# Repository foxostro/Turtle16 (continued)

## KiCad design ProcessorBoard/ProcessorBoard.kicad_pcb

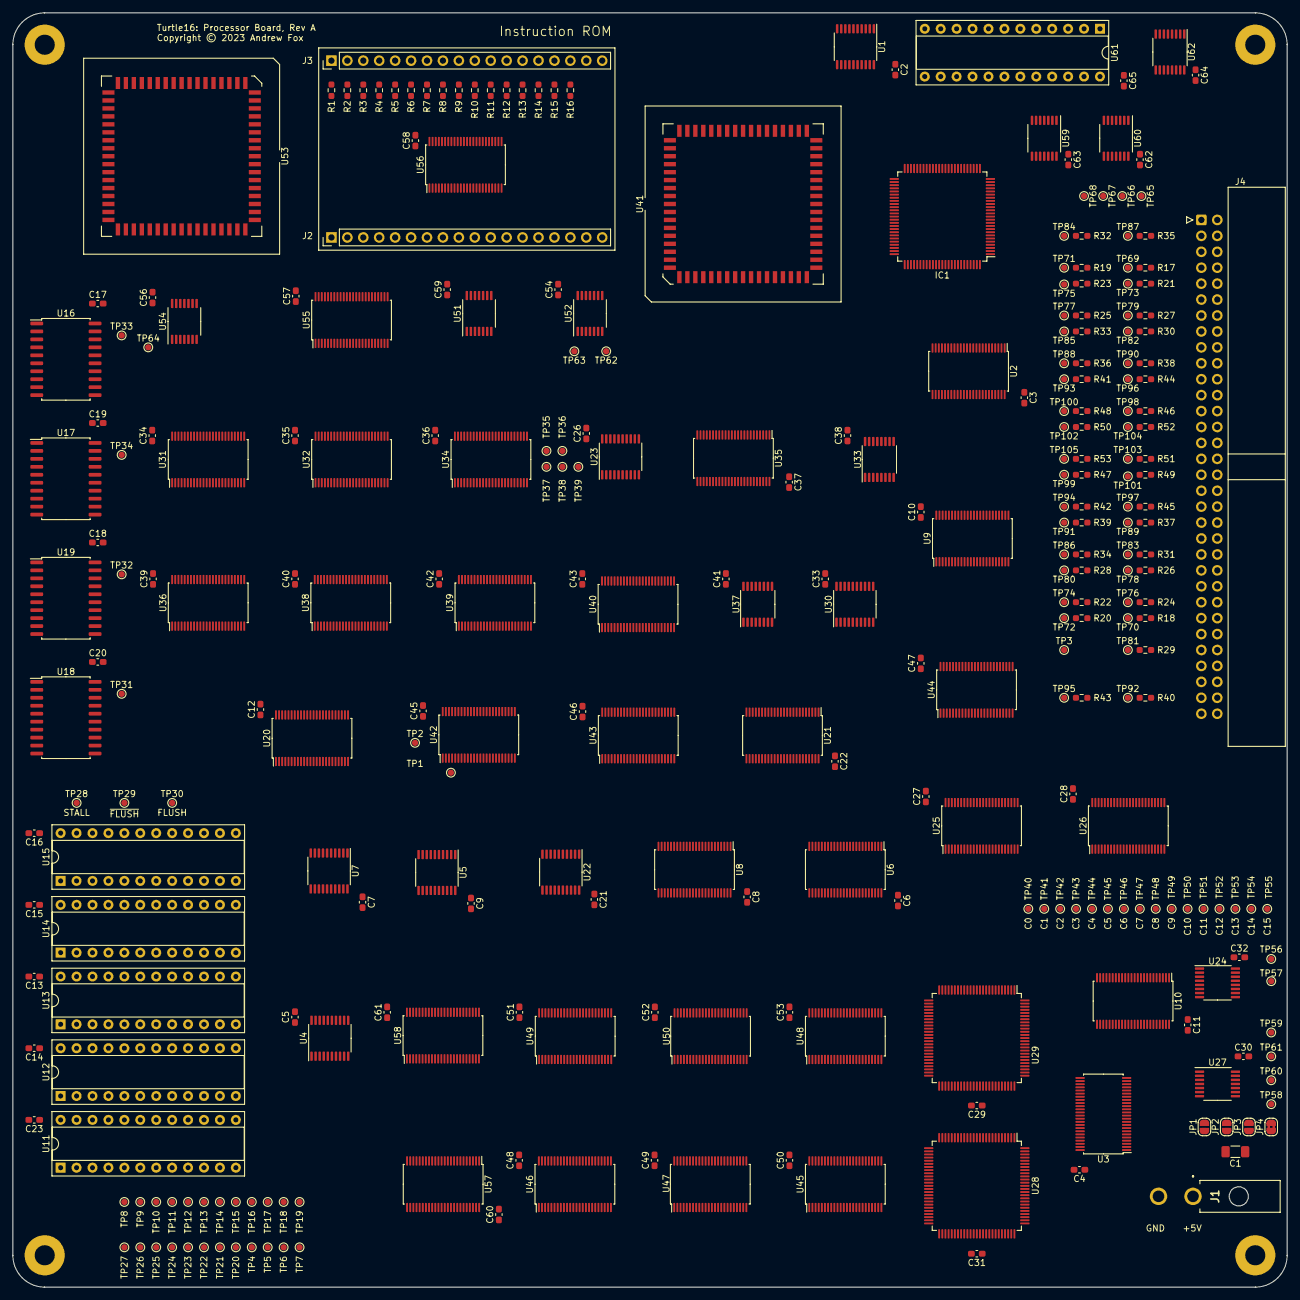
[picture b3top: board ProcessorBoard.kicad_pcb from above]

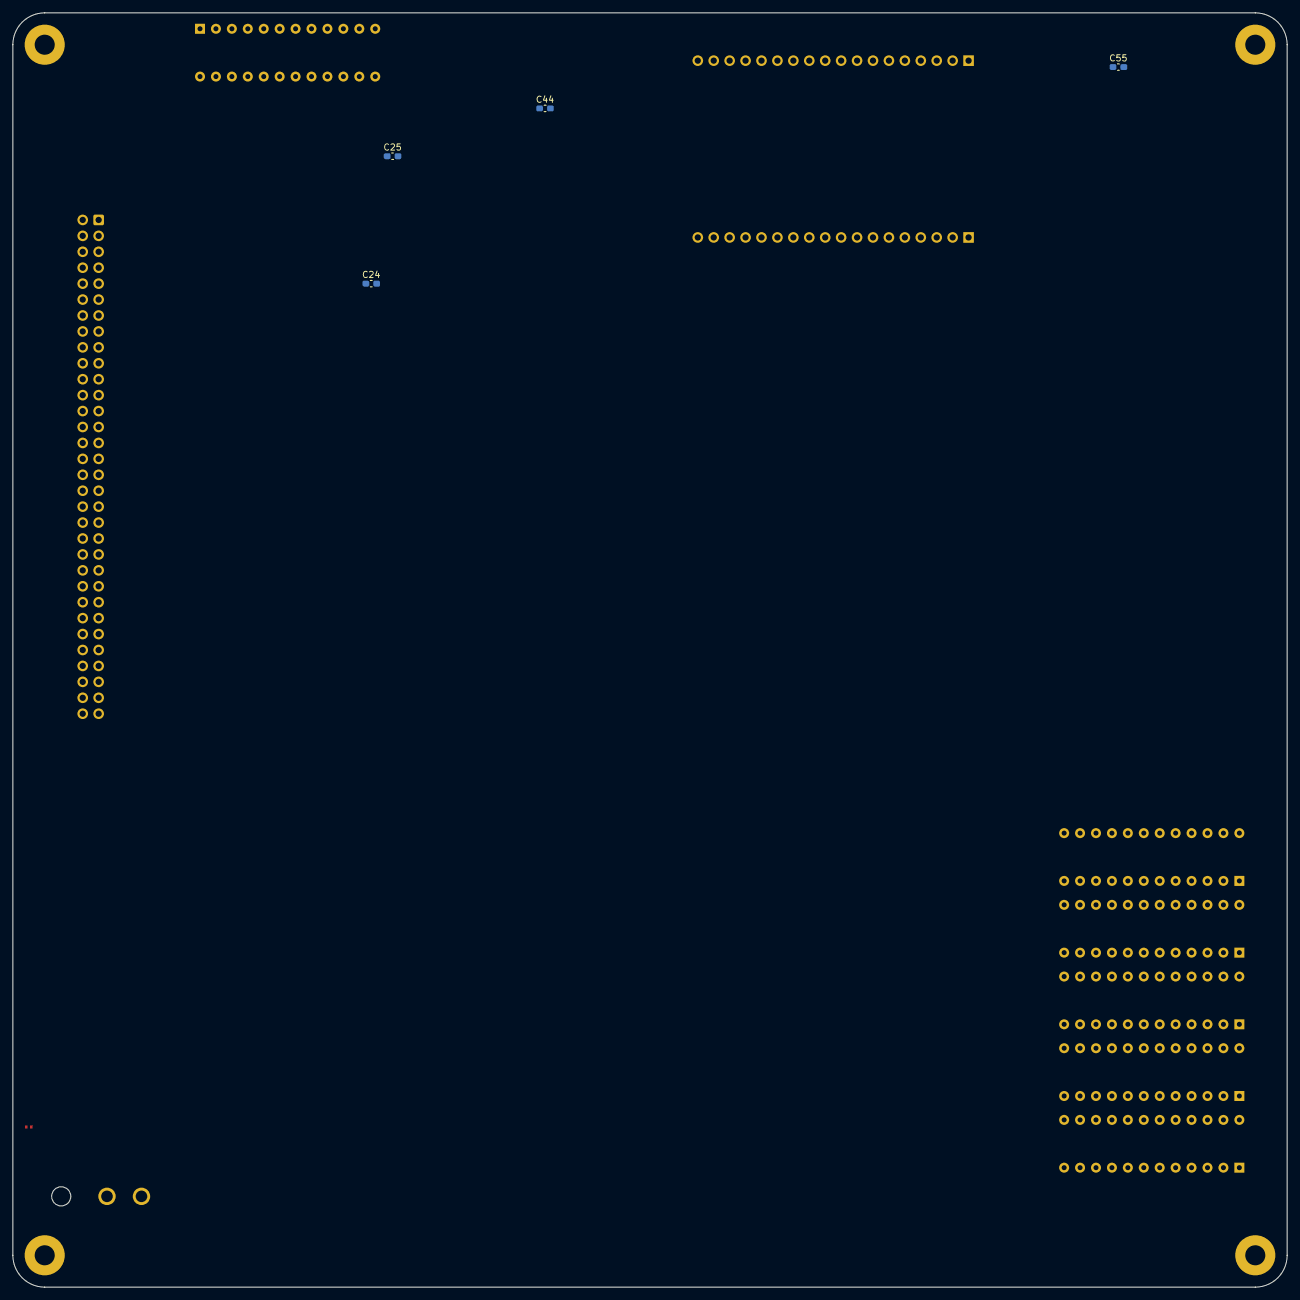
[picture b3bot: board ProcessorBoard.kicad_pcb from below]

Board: 8 copper layers, 203.2 x 203.2 mm, 298 parts (4 on the bottom side), 483 nets, no tracks yet.

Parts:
C1: 100µF; C_1206_3216Metric_Pad1.33x1.80mm_HandSolder
C2, C3, C4, C5, C6, C7, C8, C9, C10, C11, C12, C13, C14, C15, C16, C17, C18, C19, C20, C21, C22, C23, C24, C25, C33, C34, C35, C36, C37, C38, C39, C40, C41, C42, C43, C44, C45, C46, C47, C48, C49, C50, C51, C52, C53, C54, C55, C56, C57, C58, C59, C60, C61, C62, C63, C64, C65: 0.1uF; C_0603_1608Metric_Pad1.08x0.95mm_HandSolder
C26, C27, C28, C29, C30, C31, C32: 0.1µF; C_0603_1608Metric_Pad1.08x0.95mm_HandSolder
H1, H2, H3, H4: MountingHole_Pad; MountingHole_3.2mm_M3_Pad
IC1: 7028L20PFGI; TQFP-100_14x14mm_P0.5mm
J1: Power; 172448-0002
J2: UpperHeader; PinHeader_1x18_P2.54mm_Vertical
J3: LowerHeader; PinHeader_1x18_P2.54mm_Vertical
J4: 71922-164LF; IDC-Header_2x32_P2.54mm_Horizontal
JP1, JP2, JP3: SolderJumper_2_Open; SolderJumper-2_P1.3mm_Open_RoundedPad1.0x1.5mm
JP4: SolderJumper_2_Bridged; SolderJumper-2_P1.3mm_Bridged2Bar_RoundedPad1.0x1.5mm
R1, R2, R3, R4, R5, R6, R7, R8, R9, R10, R11, R12, R13, R14, R15, R16, R17, R18, R19, R20, R21, R22, R23, R24, R25, R26, R27, R28, R29, R30, R31, R32, R33, R34, R35, R36, R37, R38, R39, R41, R42, R44, R45, R46, R47, R48, R49, R50, R51, R52, R53: 10K; R_0603_1608Metric_Pad0.98x0.95mm_HandSolder
R40, R43: 1K; R_0603_1608Metric_Pad0.98x0.95mm_HandSolder
TP1: ~{MemStoreIn}; TestPoint_Pad_D1.0mm
TP2: ~{MemLoadIn}; TestPoint_Pad_D1.0mm
TP3: ~{AssertData}; TestPoint_Pad_D1.0mm
TP4: Ctl_Mid0; TestPoint_Pad_D1.0mm
TP5: Ctl_Mid1; TestPoint_Pad_D1.0mm
TP6: Ctl_Mid2; TestPoint_Pad_D1.0mm
TP7: Ctl_Mid3; TestPoint_Pad_D1.0mm
TP8: Ctl_Mid4; TestPoint_Pad_D1.0mm
TP9: Ctl_Mid5; TestPoint_Pad_D1.0mm
TP10: Ctl_Mid6; TestPoint_Pad_D1.0mm
TP11: Ctl_Mid7; TestPoint_Pad_D1.0mm
TP12: Ctl_Mid8; TestPoint_Pad_D1.0mm
TP13: Ctl_Mid9; TestPoint_Pad_D1.0mm
TP14: Ctl_Mid10; TestPoint_Pad_D1.0mm
TP15: Ctl_Mid11; TestPoint_Pad_D1.0mm
TP16: Ctl_Mid12; TestPoint_Pad_D1.0mm
TP17: Ctl_Mid13; TestPoint_Pad_D1.0mm
TP18: Ctl_Mid14; TestPoint_Pad_D1.0mm
TP19: Ctl_Mid15; TestPoint_Pad_D1.0mm
TP20: Ctl_Mid16; TestPoint_Pad_D1.0mm
TP21: Ctl_Mid17; TestPoint_Pad_D1.0mm
TP22: Ctl_Mid18; TestPoint_Pad_D1.0mm
TP23: Ctl_Mid19; TestPoint_Pad_D1.0mm
TP24: Ctl_Mid20; TestPoint_Pad_D1.0mm
TP25: Ctl_Mid21; TestPoint_Pad_D1.0mm
TP26: Ctl_Mid22; TestPoint_Pad_D1.0mm
TP27: Ctl_Mid23; TestPoint_Pad_D1.0mm
TP28: STALL; TestPoint_Pad_D1.0mm
TP29: ~{FLUSH}; TestPoint_Pad_D1.0mm
TP30: FLUSH; TestPoint_Pad_D1.0mm
TP31: SEL_B_MATCHES_SEL_C_MEM; TestPoint_Pad_D1.0mm
TP32: SEL_A_MATCHES_SEL_C_MEM; TestPoint_Pad_D1.0mm
TP33: SEL_A_MATCHES_SEL_C_EX; TestPoint_Pad_D1.0mm
TP34: SEL_B_MATCHES_SEL_C_EX; TestPoint_Pad_D1.0mm
TP35: Phi2; TestPoint_Pad_D1.0mm
TP36: Phi1a; TestPoint_Pad_D1.0mm
TP37: Phi1b; TestPoint_Pad_D1.0mm
TP38: Phi1c; TestPoint_Pad_D1.0mm
TP39: Phi1d; TestPoint_Pad_D1.0mm
TP40: C0; TestPoint_Pad_D1.0mm
TP41: C1; TestPoint_Pad_D1.0mm
TP42: C2; TestPoint_Pad_D1.0mm
TP43: C3; TestPoint_Pad_D1.0mm
TP44: C4; TestPoint_Pad_D1.0mm
TP45: C5; TestPoint_Pad_D1.0mm
TP46: C6; TestPoint_Pad_D1.0mm
TP47: C7; TestPoint_Pad_D1.0mm
TP48: C8; TestPoint_Pad_D1.0mm
TP49: C9; TestPoint_Pad_D1.0mm
TP50: C10; TestPoint_Pad_D1.0mm
TP51: C11; TestPoint_Pad_D1.0mm
TP52: C12; TestPoint_Pad_D1.0mm
TP53: C13; TestPoint_Pad_D1.0mm
TP54: C14; TestPoint_Pad_D1.0mm
TP55: C15; TestPoint_Pad_D1.0mm
TP56, TP57, TP58, TP59, TP60, TP61, TP62: TP; TestPoint_Pad_D1.0mm
TP63: RS1; TestPoint_Pad_D1.0mm
TP64: CLK; TestPoint_Pad_D1.0mm
TP65, TP66, TP67, TP68: TestPoint; TestPoint_Pad_D1.0mm
TP69: Addr0; TestPoint_Pad_D1.0mm
TP70: IO0; TestPoint_Pad_D1.0mm
TP71: Addr1; TestPoint_Pad_D1.0mm
TP72: IO1; TestPoint_Pad_D1.0mm
TP73: Addr2; TestPoint_Pad_D1.0mm
TP74: IO2; TestPoint_Pad_D1.0mm
TP75: Addr3; TestPoint_Pad_D1.0mm
TP76: IO3; TestPoint_Pad_D1.0mm
TP77: Addr4; TestPoint_Pad_D1.0mm
TP78: IO4; TestPoint_Pad_D1.0mm
TP79: Addr5; TestPoint_Pad_D1.0mm
TP80: IO5; TestPoint_Pad_D1.0mm
TP81: Bank0; TestPoint_Pad_D1.0mm
TP82: Addr6; TestPoint_Pad_D1.0mm
TP83: IO6; TestPoint_Pad_D1.0mm
TP84: Bank1; TestPoint_Pad_D1.0mm
TP85: Addr7; TestPoint_Pad_D1.0mm
TP86: IO7; TestPoint_Pad_D1.0mm
TP87: Bank2; TestPoint_Pad_D1.0mm
TP88: Addr8; TestPoint_Pad_D1.0mm
TP89: IO8; TestPoint_Pad_D1.0mm
TP90: Addr9; TestPoint_Pad_D1.0mm
TP91: IO9; TestPoint_Pad_D1.0mm
TP92: ~{MemStore}; TestPoint_Pad_D1.0mm
TP93: Addr10; TestPoint_Pad_D1.0mm
TP94: IO10; TestPoint_Pad_D1.0mm
TP95: ~{MemLoad}; TestPoint_Pad_D1.0mm
TP96: Addr11; TestPoint_Pad_D1.0mm
TP97: IO11; TestPoint_Pad_D1.0mm
TP98: Addr12; TestPoint_Pad_D1.0mm
TP99: IO12; TestPoint_Pad_D1.0mm
TP100: Addr13; TestPoint_Pad_D1.0mm
TP101: IO13; TestPoint_Pad_D1.0mm
TP102: Addr14; TestPoint_Pad_D1.0mm
TP103: IO14; TestPoint_Pad_D1.0mm
TP104: Addr15; TestPoint_Pad_D1.0mm
TP105: IO15; TestPoint_Pad_D1.0mm
U1, U23: 74AHCT245; TSSOP-20_4.4x6.5mm_P0.65mm
U2, U3, U6, U8, U31, U32, U34, U35, U36, U38, U39, U40, U45, U46, U47, U48, U49, U50: 74AHCT16245; TSSOP-48_6.1x12.5mm_P0.5mm
U4: 74ABT574; TSSOP-20_4.4x6.5mm_P0.65mm
U5, U7: 74HC245; TSSOP-20_4.4x6.5mm_P0.65mm
U9, U10, U20, U21, U42, U43, U44, U55, U56, U57, U58: 74ABT16374; TSSOP-48_6.1x12.5mm_P0.5mm
U11, U12, U13, U14, U15: ATF22V10C-7PX; DIP-24_W7.62mm_Socket
U16, U17, U18, U19: 74F521; SOIC-20W_7.5x12.8mm_P1.27mm
U22: 74AHCT574; TSSOP-20_4.4x6.5mm_P0.65mm
U24, U33, U37: 74AHCT138; TSSOP-16_4.4x5mm_P0.65mm
U25, U26: 74ABT16245; TSSOP-48_6.1x12.5mm_P0.5mm
U27: 74AHCT32; TSSOP-14_4.4x5mm_P0.65mm
U28, U29: IDT7024L15PFG; TQFP-100_14x14mm_P0.5mm
U30: 74ABT377; TSSOP-20_4.4x6.5mm_P0.65mm
U41, U53: IDT7381; PLCC-68_SMD-Socket
U51, U54, U59: 74ABT32; TSSOP-14_4.4x5mm_P0.65mm
U52, U60: 74AHCT04; TSSOP-14_4.4x5mm_P0.65mm
U61: ATF22V10C; DIP-24_W7.62mm_Socket
U62: CD74HC173PWR; TSSOP-16_4.4x5mm_P0.65mm

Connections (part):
/EX/A0: U41.1 (A0), U57.2 (1Q1)
/EX/A1: U41.2 (A1), U57.3 (1Q2)
/EX/A2: U41.3 (A2), U57.5 (1Q3)
/EX/A3: U41.4 (A3), U57.6 (1Q4)
/EX/A4: U41.5 (A4), U57.8 (1Q5)
/EX/A5: U41.6 (A5), U57.9 (1Q6)
/EX/A6: U41.7 (A6), U57.11 (1Q7)
/EX/A7: U41.8 (A7), U57.12 (1Q8)
/EX/A8: U41.9 (A8), U57.13 (2Q1)
/EX/A9: U41.10 (A9), U57.14 (2Q2)
/EX/A10: U41.11 (A10), U57.16 (2Q3)
/EX/A11: U41.12 (A11), U57.17 (2Q4)
/EX/A12: U41.13 (A12), U57.19 (2Q5)
/EX/A13: U41.14 (A13), U57.20 (2Q6)
/EX/A14: U41.15 (A14), U57.22 (2Q7)
/EX/A15: U41.16 (A15), U57.23 (2Q8)
/EX/ALU/C16: U30.3 (D0), U41.20 (C16)
/EX/ALU/OVF: U30.7 (D2), U41.24 (OVF)
/EX/ALU/RightOp0: U31.2 (1B1), U32.2 (1B1), U34.2 (1B1), U35.2 (1B1), U41.53 (B0)
/EX/ALU/RightOp1: U31.3 (1B2), U32.3 (1B2), U34.3 (1B2), U35.3 (1B2), U41.54 (B1)
/EX/ALU/RightOp2: U31.5 (1B3), U32.5 (1B3), U34.5 (1B3), U35.5 (1B3), U41.55 (B2)
/EX/ALU/RightOp3: U31.6 (1B4), U32.6 (1B4), U34.6 (1B4), U35.6 (1B4), U41.56 (B3)
/EX/ALU/RightOp4: U31.8 (1B5), U32.8 (1B5), U34.8 (1B5), U35.8 (1B5), U41.57 (B4)
/EX/ALU/RightOp5: U31.9 (1B6), U32.9 (1B6), U34.9 (1B6), U35.9 (1B6), U41.58 (B5)
/EX/ALU/RightOp6: U31.11 (1B7), U32.11 (1B7), U34.11 (1B7), U35.11 (1B7), U41.59 (B6)
/EX/ALU/RightOp7: U31.12 (1B8), U32.12 (1B8), U34.12 (1B8), U35.12 (1B8), U41.60 (B7)
/EX/ALU/RightOp8: U31.13 (2B1), U32.13 (2B1), U34.13 (2B1), U35.13 (2B1), U41.61 (B8)
/EX/ALU/RightOp9: U31.14 (2B2), U32.14 (2B2), U34.14 (2B2), U35.14 (2B2), U41.62 (B9)
/EX/ALU/RightOp10: U31.16 (2B3), U32.16 (2B3), U34.16 (2B3), U35.16 (2B3), U41.63 (B10)
/EX/ALU/RightOp11: U31.17 (2B4), U32.17 (2B4), U34.17 (2B4), U35.17 (2B4), U41.64 (B11)
/EX/ALU/RightOp12: U31.19 (2B5), U32.19 (2B5), U34.19 (2B5), U35.19 (2B5), U41.65 (B12)
/EX/ALU/RightOp13: U31.20 (2B6), U32.20 (2B6), U34.20 (2B6), U35.20 (2B6), U41.66 (B13)
/EX/ALU/RightOp14: U31.22 (2B7), U32.22 (2B7), U34.22 (2B7), U35.22 (2B7), U41.67 (B14)
/EX/ALU/RightOp15: U31.23 (2B8), U32.23 (2B8), U34.23 (2B8), U35.23 (2B8), U41.68 (B15)
/EX/ALU/Z: U30.4 (D1), U41.23 (Z)
/EX/B0: U31.47 (1A1), U36.47 (1A1), U58.2 (1Q1)
/EX/B1: U31.46 (1A2), U36.46 (1A2), U58.3 (1Q2)
/EX/B2: U31.44 (1A3), U36.44 (1A3), U58.5 (1Q3)
/EX/B3: U31.43 (1A4), U36.43 (1A4), U58.6 (1Q4)
/EX/B4: U31.41 (1A5), U36.41 (1A5), U58.8 (1Q5)
/EX/B5: U31.40 (1A6), U36.40 (1A6), U58.9 (1Q6)
/EX/B6: U31.38 (1A7), U36.38 (1A7), U58.11 (1Q7)
/EX/B7: U31.37 (1A8), U36.37 (1A8), U58.12 (1Q8)
/EX/B8: U31.36 (2A1), U36.36 (2A1), U58.13 (2Q1)
/EX/B9: U31.35 (2A2), U36.35 (2A2), U58.14 (2Q2)
/EX/B10: U31.33 (2A3), U36.33 (2A3), U58.16 (2Q3)
/EX/B11: U31.32 (2A4), U36.32 (2A4), U58.17 (2Q4)
/EX/B12: U31.30 (2A5), U36.30 (2A5), U58.19 (2Q5)
/EX/B13: U31.29 (2A6), U36.29 (2A6), U58.20 (2Q6)
/EX/B14: U31.27 (2A7), U36.27 (2A7), U58.22 (2Q7)
/EX/B15: U31.26 (2A8), U36.26 (2A8), U58.23 (2Q8)
/EX/Carry: U11.4 (IN), U12.4 (IN), U13.4 (IN), U30.2 (Q0)
/EX/Ctl_MEM14: TP2.1, U1.3 (A1), U42.2 (1Q1)
/EX/Ctl_MEM15: TP1.1, U1.2 (A0), U42.3 (1Q2)
/EX/Ctl_MEM16: U42.5 (1Q3), U59.1
/EX/Ctl_MEM17: U4.9 (D7), U14.4 (IN), U42.6 (1Q4)
/EX/Ctl_MEM18: U4.8 (D6), U42.8 (1Q5)
/EX/Ctl_MEM19: U4.7 (D5), U42.9 (1Q6)
/EX/Ctl_MEM20: U4.6 (D4), U14.5 (IN), U42.11 (1Q7)
/EX/N: U11.1 (IN/CLK), U12.1 (IN/CLK), U13.1 (IN/CLK), U30.9 (Q3)
/EX/OVF: U11.2 (IN), U12.2 (IN), U13.2 (IN), U30.6 (Q2)
/EX/PC_EX0: U38.47 (1A1), U55.2 (1Q1)
/EX/PC_EX1: U38.46 (1A2), U55.3 (1Q2)
/EX/PC_EX2: U38.44 (1A3), U55.5 (1Q3)
/EX/PC_EX3: U38.43 (1A4), U55.6 (1Q4)
/EX/PC_EX4: U38.41 (1A5), U55.8 (1Q5)
/EX/PC_EX5: U38.40 (1A6), U55.9 (1Q6)
/EX/PC_EX6: U38.38 (1A7), U55.11 (1Q7)
/EX/PC_EX7: U38.37 (1A8), U55.12 (1Q8)
/EX/PC_EX8: U38.36 (2A1), U55.13 (2Q1)
/EX/PC_EX9: U38.35 (2A2), U55.14 (2Q2)
/EX/PC_EX10: U38.33 (2A3), U55.16 (2Q3)
/EX/PC_EX11: U38.32 (2A4), U55.17 (2Q4)
/EX/PC_EX12: U38.30 (2A5), U55.19 (2Q5)
/EX/PC_EX13: U38.29 (2A6), U55.20 (2Q6)
/EX/PC_EX14: U38.27 (2A7), U55.22 (2Q7)
/EX/PC_EX15: U38.26 (2A8), U55.23 (2Q8)
/EX/SelC_MEM0: U4.5 (D3), U18.3 (Q0), U19.3 (Q0), U42.13 (2Q1)
/EX/SelC_MEM1: U4.4 (D2), U18.5 (Q1), U19.5 (Q1), U42.14 (2Q2)
/EX/SelC_MEM2: U4.3 (D1), U18.7 (Q2), U19.7 (Q2), U42.16 (2Q3)
/EX/StoreOp_MEM0: U2.23 (2B8), U43.2 (1Q1)
/EX/StoreOp_MEM1: U2.22 (2B7), U43.3 (1Q2)
/EX/StoreOp_MEM2: U2.20 (2B6), U43.5 (1Q3)
/EX/StoreOp_MEM3: U2.19 (2B5), U43.6 (1Q4)
/EX/StoreOp_MEM4: U2.17 (2B4), U43.8 (1Q5)
/EX/StoreOp_MEM5: U2.16 (2B3), U43.9 (1Q6)
/EX/StoreOp_MEM6: U2.14 (2B2), U43.11 (1Q7)
/EX/StoreOp_MEM7: U2.13 (2B1), U43.12 (1Q8)
/EX/StoreOp_MEM8: U2.12 (1B8), U43.13 (2Q1)
/EX/StoreOp_MEM9: U2.11 (1B7), U43.14 (2Q2)
/EX/StoreOp_MEM10: U2.9 (1B6), U43.16 (2Q3)
/EX/StoreOp_MEM11: U2.8 (1B5), U43.17 (2Q4)
/EX/StoreOp_MEM12: U2.6 (1B4), U43.19 (2Q5)
/EX/StoreOp_MEM13: U2.5 (1B3), U43.20 (2Q6)
/EX/StoreOp_MEM14: U2.3 (1B2), U43.22 (2Q7)
/EX/StoreOp_MEM15: U2.2 (1B1), U43.23 (2Q8)
/EX/Y_EX0: U41.43 (F0), U44.47 (1D1), U46.47 (1A1), U49.47 (1A1), U53.53 (B0)
/EX/Y_EX1: U41.42 (F1), U44.46 (1D2), U46.46 (1A2), U49.46 (1A2), U53.54 (B1)
/EX/Y_EX2: U41.41 (F2), U44.44 (1D3), U46.44 (1A3), U49.44 (1A3), U53.55 (B2)
/EX/Y_EX3: U41.40 (F3), U44.43 (1D4), U46.43 (1A4), U49.43 (1A4), U53.56 (B3)
/EX/Y_EX4: U41.39 (F4), U44.41 (1D5), U46.41 (1A5), U49.41 (1A5), U53.57 (B4)
/EX/Y_EX5: U41.38 (F5), U44.40 (1D6), U46.40 (1A6), U49.40 (1A6), U53.58 (B5)
/EX/Y_EX6: U41.37 (F6), U44.38 (1D7), U46.38 (1A7), U49.38 (1A7), U53.59 (B6)
/EX/Y_EX7: U41.36 (F7), U44.37 (1D8), U46.37 (1A8), U49.37 (1A8), U53.60 (B7)
/EX/Y_EX8: U41.35 (F8), U44.36 (2D1), U46.36 (2A1), U49.36 (2A1), U53.61 (B8)
/EX/Y_EX9: U41.34 (F9), U44.35 (2D2), U46.35 (2A2), U49.35 (2A2), U53.62 (B9)
/EX/Y_EX10: U41.33 (F10), U44.33 (2D3), U46.33 (2A3), U49.33 (2A3), U53.63 (B10)
/EX/Y_EX11: U41.32 (F11), U44.32 (2D4), U46.32 (2A4), U49.32 (2A4), U53.64 (B11)
/EX/Y_EX12: U41.31 (F12), U44.30 (2D5), U46.30 (2A5), U49.30 (2A5), U53.65 (B12)
/EX/Y_EX13: U41.30 (F13), U44.29 (2D6), U46.29 (2A6), U49.29 (2A6), U53.66 (B13)
/EX/Y_EX14: U41.29 (F14), U44.27 (2D7), U46.27 (2A7), U49.27 (2A7), U53.67 (B14)
/EX/Y_EX15: U30.8 (D3), U41.28 (F15), U44.26 (2D8), U46.26 (2A8), U49.26 (2A8), U53.68 (B15)
/EX/Y_MEM0: U3.2 (1B1), U10.47 (1D1), U44.2 (1Q1), U47.47 (1A1), U50.47 (1A1)
/EX/Y_MEM1: U3.3 (1B2), U10.46 (1D2), U44.3 (1Q2), U47.46 (1A2), U50.46 (1A2)
/EX/Y_MEM2: U3.5 (1B3), U10.44 (1D3), U44.5 (1Q3), U47.44 (1A3), U50.44 (1A3)
/EX/Y_MEM3: U3.6 (1B4), U10.43 (1D4), U44.6 (1Q4), U47.43 (1A4), U50.43 (1A4)
/EX/Y_MEM4: U3.8 (1B5), U10.41 (1D5), U44.8 (1Q5), U47.41 (1A5), U50.41 (1A5)
/EX/Y_MEM5: U3.9 (1B6), U10.40 (1D6), U44.9 (1Q6), U47.40 (1A6), U50.40 (1A6)
/EX/Y_MEM6: U3.11 (1B7), U10.38 (1D7), U44.11 (1Q7), U47.38 (1A7), U50.38 (1A7)
/EX/Y_MEM7: U3.12 (1B8), U10.37 (1D8), U44.12 (1Q8), U47.37 (1A8), U50.37 (1A8)
/EX/Y_MEM8: U3.13 (2B1), U10.36 (2D1), U44.13 (2Q1), U47.36 (2A1), U50.36 (2A1)
/EX/Y_MEM9: U3.14 (2B2), U10.35 (2D2), U44.14 (2Q2), U47.35 (2A2), U50.35 (2A2)
/EX/Y_MEM10: U3.16 (2B3), U10.33 (2D3), U44.16 (2Q3), U47.33 (2A3), U50.33 (2A3)
/EX/Y_MEM11: U3.17 (2B4), U10.32 (2D4), U44.17 (2Q4), U47.32 (2A4), U50.32 (2A4)
/EX/Y_MEM12: U3.19 (2B5), U10.30 (2D5), U44.19 (2Q5), U47.30 (2A5), U50.30 (2A5)
/EX/Y_MEM13: U3.20 (2B6), U10.29 (2D6), U44.20 (2Q6), U47.29 (2A6), U50.29 (2A6)
/EX/Y_MEM14: U3.22 (2B7), U10.27 (2D7), U44.22 (2Q7), U47.27 (2A7), U50.27 (2A7)
/EX/Y_MEM15: U3.23 (2B8), U10.26 (2D8), U44.23 (2Q8), U47.26 (2A8), U50.26 (2A8)
/EX/Z: U11.3 (IN), U12.3 (IN), U13.3 (IN), U30.5 (Q1)
/EX/sheet5FD8D6EA/StoreOp_EX0: U36.2 (1B1), U38.2 (1B1), U39.2 (1B1), U40.2 (1B1), U43.47 (1D1)
/EX/sheet5FD8D6EA/StoreOp_EX1: U36.3 (1B2), U38.3 (1B2), U39.3 (1B2), U40.3 (1B2), U43.46 (1D2)
/EX/sheet5FD8D6EA/StoreOp_EX2: U36.5 (1B3), U38.5 (1B3), U39.5 (1B3), U40.5 (1B3), U43.44 (1D3)
/EX/sheet5FD8D6EA/StoreOp_EX3: U36.6 (1B4), U38.6 (1B4), U39.6 (1B4), U40.6 (1B4), U43.43 (1D4)
/EX/sheet5FD8D6EA/StoreOp_EX4: U36.8 (1B5), U38.8 (1B5), U39.8 (1B5), U40.8 (1B5), U43.41 (1D5)
/EX/sheet5FD8D6EA/StoreOp_EX5: U36.9 (1B6), U38.9 (1B6), U39.9 (1B6), U40.9 (1B6), U43.40 (1D6)
/EX/sheet5FD8D6EA/StoreOp_EX6: U36.11 (1B7), U38.11 (1B7), U39.11 (1B7), U40.11 (1B7), U43.38 (1D7)
/EX/sheet5FD8D6EA/StoreOp_EX7: U36.12 (1B8), U38.12 (1B8), U39.12 (1B8), U40.12 (1B8), U43.37 (1D8)
/EX/sheet5FD8D6EA/StoreOp_EX8: U36.13 (2B1), U38.13 (2B1), U39.13 (2B1), U40.13 (2B1), U43.36 (2D1)
/EX/sheet5FD8D6EA/StoreOp_EX9: U36.14 (2B2), U38.14 (2B2), U39.14 (2B2), U40.14 (2B2), U43.35 (2D2)
/EX/sheet5FD8D6EA/StoreOp_EX10: U36.16 (2B3), U38.16 (2B3), U39.16 (2B3), U40.16 (2B3), U43.33 (2D3)
/EX/sheet5FD8D6EA/StoreOp_EX11: U36.17 (2B4), U38.17 (2B4), U39.17 (2B4), U40.17 (2B4), U43.32 (2D4)
/EX/sheet5FD8D6EA/StoreOp_EX12: U36.19 (2B5), U38.19 (2B5), U39.19 (2B5), U40.19 (2B5), U43.30 (2D5)
/EX/sheet5FD8D6EA/StoreOp_EX13: U36.20 (2B6), U38.20 (2B6), U39.20 (2B6), U40.20 (2B6), U43.29 (2D6)
/EX/sheet5FD8D6EA/StoreOp_EX14: U36.22 (2B7), U38.22 (2B7), U39.22 (2B7), U40.22 (2B7), U43.27 (2D7)
/EX/sheet5FD8D6EA/StoreOp_EX15: U36.23 (2B8), U38.23 (2B8), U39.23 (2B8), U40.23 (2B8), U43.26 (2D8)
/ID/Ctl_EX0: J4.60, U21.2 (1Q1)
/ID/Ctl_EX1: U21.3 (1Q2), U37.1 (A0)
/ID/Ctl_EX2: U21.5 (1Q3), U37.2 (A1)
/ID/Ctl_EX3: U21.6 (1Q4), U33.1 (A0)
/ID/Ctl_EX4: U21.8 (1Q5), U33.2 (A1)
/ID/Ctl_EX5: U15.4 (IN), U21.9 (1Q6), U30.1 (~E)
/ID/Ctl_EX6: U21.11 (1Q7), U41.44 (C0)
/ID/Ctl_EX7: U21.12 (1Q8), U41.45 (I0)
/ID/Ctl_EX8: U21.13 (2Q1), U41.46 (I1)
/ID/Ctl_EX9: U21.14 (2Q2), U41.47 (I2)
/ID/Ctl_EX10: U21.16 (2Q3), U41.48 (RS0)
/ID/Ctl_EX11: U21.17 (2Q4), U41.49 (RS1)
/ID/Ctl_EX12: U15.5 (IN), U21.19 (2Q5), U52.1, U53.44 (C0)
/ID/Ctl_EX13: U21.20 (2Q6), U53.48 (RS0)
/ID/Ctl_EX14: U21.22 (2Q7), U42.47 (1D1)
/ID/Ctl_EX15: U21.23 (2Q8), U42.46 (1D2)
/ID/Ctl_EX16: U22.12 (Q7), U42.44 (1D3)
/ID/Ctl_EX17: U14.2 (IN), U22.13 (Q6), U42.43 (1D4)
/ID/Ctl_EX18: U22.14 (Q5), U42.41 (1D5)
/ID/Ctl_EX19: U22.15 (Q4), U42.40 (1D6)
/ID/Ctl_EX20: U14.3 (IN), U22.16 (Q3), U42.38 (1D7)
/ID/Ctl_Mid0: TP4.1, U6.47 (1A1), U11.23 (I/O)
/ID/Ctl_Mid1: TP5.1, U6.46 (1A2), U11.22 (I/O)
/ID/Ctl_Mid2: TP6.1, U6.44 (1A3), U11.21 (I/O)
/ID/Ctl_Mid3: TP7.1, U6.43 (1A4), U11.20 (I/O)
/ID/Ctl_Mid4: TP8.1, U6.41 (1A5), U11.19 (I/O)
/ID/Ctl_Mid5: TP9.1, U6.40 (1A6), U11.16 (I/O)
/ID/Ctl_Mid6: TP10.1, U6.38 (1A7), U11.17 (I/O)
/ID/Ctl_Mid7: TP11.1, U6.37 (1A8), U11.14 (I/O)
/ID/Ctl_Mid8: TP12.1, U6.36 (2A1), U11.15 (I/O)
/ID/Ctl_Mid9: TP13.1, U6.35 (2A2), U11.18 (I/O)
/ID/Ctl_Mid10: TP14.1, U6.33 (2A3), U12.19 (I/O)
/ID/Ctl_Mid11: TP15.1, U6.32 (2A4), U12.23 (I/O)
/ID/Ctl_Mid12: TP16.1, U6.30 (2A5), U12.21 (I/O)
/ID/Ctl_Mid13: TP17.1, U6.29 (2A6), U12.20 (I/O)
/ID/Ctl_Mid14: TP18.1, U6.27 (2A7), U12.22 (I/O)
/ID/Ctl_Mid15: TP19.1, U6.26 (2A8), U12.18 (I/O)
/ID/Ctl_Mid16: TP20.1, U5.11 (B7), U12.17 (I/O)
/ID/Ctl_Mid17: TP21.1, U5.12 (B6), U12.16 (I/O)
/ID/Ctl_Mid18: TP22.1, U5.13 (B5), U12.15 (I/O)
/ID/Ctl_Mid19: TP23.1, U5.14 (B4), U12.14 (I/O)
/ID/Ctl_Mid20: TP24.1, U5.15 (B3), U13.23 (I/O)
/ID/Ctl_Mid21: TP25.1, U5.16 (B2), U13.22 (I/O), U14.10 (IN)
/ID/Ctl_Mid22: TP26.1, U5.17 (B1), U13.21 (I/O), U14.11 (IN)
/ID/Ctl_Mid23: TP27.1, U5.18 (B0), U13.20 (I/O)
/ID/FWD_A: U14.21 (I/O), U45.25 (2~OE), U45.48 (1~OE)
/ID/FWD_B: U14.20 (I/O), U48.25 (2~OE), U48.48 (1~OE)
/ID/FWD_EX_TO_A: U14.22 (I/O), U46.25 (2~OE), U46.48 (1~OE)
/ID/FWD_EX_TO_B: U14.19 (I/O), U49.25 (2~OE), U49.48 (1~OE)
/ID/FWD_MEM_TO_A: U14.23 (I/O), U47.25 (2~OE), U47.48 (1~OE)
/ID/FWD_MEM_TO_B: U14.18 (I/O), U50.25 (2~OE), U50.48 (1~OE)
/ID/Hazard Control/FLUSH: TP30.1, U5.19 (CE), U6.25 (2~OE), U6.48 (1~OE), U15.21 (I/O)
/ID/Hazard Control/Hazard Control Comparators/SEL_A_MATCHES_SEL_C_EX: TP33.1, U14.6 (IN), U16.19 (~P=Q)
/ID/Hazard Control/Hazard Control Comparators/SEL_A_MATCHES_SEL_C_MEM: TP32.1, U14.8 (IN), U19.19 (~P=Q)
/ID/Hazard Control/Hazard Control Comparators/SEL_B_MATCHES_SEL_C_EX: TP34.1, U14.7 (IN), U17.19 (~P=Q)
/ID/Hazard Control/Hazard Control Comparators/SEL_B_MATCHES_SEL_C_MEM: TP31.1, U14.9 (IN), U18.19 (~P=Q)
/ID/Hazard Control/STALL: TP28.1, U15.23 (I/O), U53.25 (~ENF), U54.2
/ID/Hazard Control/~FLUSH: TP29.1, U7.19 (CE), U8.25 (2~OE), U8.48 (1~OE), U15.22 (I/O)
/ID/ID Flush/Ctl_ID0: U6.2 (1B1), U8.47 (1A1), U21.47 (1D1)
/ID/ID Flush/Ctl_ID1: U6.3 (1B2), U8.46 (1A2), U21.46 (1D2)
/ID/ID Flush/Ctl_ID2: U6.5 (1B3), U8.44 (1A3), U21.44 (1D3)
/ID/ID Flush/Ctl_ID3: U6.6 (1B4), U8.43 (1A4), U21.43 (1D4)
/ID/ID Flush/Ctl_ID4: U6.8 (1B5), U8.41 (1A5), U21.41 (1D5)
/ID/ID Flush/Ctl_ID5: U6.9 (1B6), U8.40 (1A6), U21.40 (1D6)
/ID/ID Flush/Ctl_ID6: U6.11 (1B7), U8.38 (1A7), U21.38 (1D7)
/ID/ID Flush/Ctl_ID7: U6.12 (1B8), U8.37 (1A8), U21.37 (1D8)
/ID/ID Flush/Ctl_ID8: U6.13 (2B1), U8.36 (2A1), U21.36 (2D1)
/ID/ID Flush/Ctl_ID9: U6.14 (2B2), U8.35 (2A2), U21.35 (2D2)
/ID/ID Flush/Ctl_ID10: U6.16 (2B3), U8.33 (2A3), U21.33 (2D3)
/ID/ID Flush/Ctl_ID11: U6.17 (2B4), U8.32 (2A4), U21.32 (2D4)
/ID/ID Flush/Ctl_ID12: U6.19 (2B5), U8.30 (2A5), U21.30 (2D5)
/ID/ID Flush/Ctl_ID13: U6.20 (2B6), U8.29 (2A6), U21.29 (2D6)
/ID/ID Flush/Ctl_ID14: U6.22 (2B7), U8.27 (2A7), U21.27 (2D7)
/ID/ID Flush/Ctl_ID15: U6.23 (2B8), U8.26 (2A8), U21.26 (2D8)
/ID/ID Flush/Ctl_ID16: U5.9 (A7), U7.11 (B7), U22.9 (D7)
/ID/ID Flush/Ctl_ID17: U5.8 (A6), U7.12 (B6), U22.8 (D6)
/ID/ID Flush/Ctl_ID18: U5.7 (A5), U7.13 (B5), U22.7 (D5)
/ID/ID Flush/Ctl_ID19: U5.6 (A4), U7.14 (B4), U22.6 (D4)
/ID/ID Flush/Ctl_ID20: U5.5 (A3), U7.15 (B3), U22.5 (D3)
/ID/ID Flush/Ctl_ID21: U5.4 (A2), U7.16 (B2), U22.4 (D2)
/ID/ID Flush/Ctl_ID22: U5.3 (A1), U7.17 (B1), U22.3 (D1)
/ID/ID Flush/Ctl_ID23: U5.2 (A0), U7.18 (B0), U22.2 (D0)
/ID/Ins_EX0: U20.2 (1Q1), U32.47 (1A1), U34.47 (1A1), U35.47 (1A1), U39.47 (1A1), U40.36 (2A1)
/ID/Ins_EX1: U20.3 (1Q2), U32.46 (1A2), U34.46 (1A2), U35.46 (1A2), U39.46 (1A2), U40.35 (2A2)
/ID/Ins_EX2: U20.5 (1Q3), U32.44 (1A3), U35.44 (1A3), U39.44 (1A3), U40.33 (2A3)
/ID/Ins_EX3: U20.6 (1Q4), U32.43 (1A4), U35.43 (1A4), U39.43 (1A4), U40.32 (2A4)
/ID/Ins_EX4: U20.8 (1Q5), U32.26 (2A8), U32.27 (2A7), U32.29 (2A6), U32.30 (2A5), U32.32 (2A4), U32.33 (2A3), U32.35 (2A2), U32.36 (2A1), U32.37 (1A8), U32.38 (1A7), U32.40 (1A6), U32.41 (1A5), U35.41 (1A5), U39.41 (1A5), U40.30 (2A5)
/ID/Ins_EX5: U20.9 (1Q6), U35.40 (1A6), U39.40 (1A6), U40.29 (2A6)
/ID/Ins_EX6: U20.11 (1Q7), U35.38 (1A7), U39.38 (1A7), U40.27 (2A7)
/ID/Ins_EX7: U20.12 (1Q8), U35.37 (1A8), U39.26 (2A8), U39.27 (2A7), U39.29 (2A6), U39.30 (2A5), U39.32 (2A4), U39.33 (2A3), U39.35 (2A2), U39.36 (2A1), U39.37 (1A8), U40.26 (2A8)
/ID/Ins_EX8: U16.3 (Q0), U17.3 (Q0), U20.13 (2Q1), U34.44 (1A3), U35.36 (2A1), U42.36 (2D1)
/ID/Ins_EX9: U16.5 (Q1), U17.5 (Q1), U20.14 (2Q2), U34.43 (1A4), U35.35 (2A2), U42.35 (2D2)
/ID/Ins_EX10: U16.7 (Q2), U17.7 (Q2), U20.16 (2Q3), U34.26 (2A8), U34.27 (2A7), U34.29 (2A6), U34.30 (2A5), U34.32 (2A4), U34.33 (2A3), U34.35 (2A2), U34.36 (2A1), U34.37 (1A8), U34.38 (1A7), U34.40 (1A6), U34.41 (1A5), U35.26 (2A8), U35.27 (2A7), U35.29 (2A6), U35.30 (2A5), U35.32 (2A4), U35.33 (2A3), U42.33 (2D3)
/ID/Ins_ID0: U20.47 (1D1), U56.2 (1Q1)
/ID/Ins_ID1: U20.46 (1D2), U56.3 (1Q2)
/ID/Ins_ID2: U17.2 (P0), U18.2 (P0), U20.44 (1D3), U29.59 (A0R), U56.5 (1Q3)
/ID/Ins_ID3: U17.4 (P1), U18.4 (P1), U20.43 (1D4), U29.58 (A1R), U56.6 (1Q4)
/ID/Ins_ID4: U17.6 (P2), U18.6 (P2), U20.41 (1D5), U29.57 (A2R), U56.8 (1Q5)
/ID/Ins_ID5: U16.2 (P0), U19.2 (P0), U20.40 (1D6), U28.59 (A0R), U56.9 (1Q6)
/ID/Ins_ID6: U16.4 (P1), U19.4 (P1), U20.38 (1D7), U28.58 (A1R), U56.11 (1Q7)
/ID/Ins_ID7: U16.6 (P2), U19.6 (P2), U20.37 (1D8), U28.57 (A2R), U56.12 (1Q8)
/ID/Ins_ID8: U20.36 (2D1), U56.13 (2Q1)
/ID/Ins_ID9: U20.35 (2D2), U56.14 (2Q2)
/ID/Ins_ID10: U20.33 (2D3), U56.16 (2Q3)
/ID/Ins_ID11: U11.9 (IN), U12.9 (IN), U13.9 (IN), U56.17 (2Q4)
/ID/Ins_ID12: U11.8 (IN), U12.8 (IN), U13.8 (IN), U56.19 (2Q5)
/ID/Ins_ID13: U11.7 (IN), U12.7 (IN), U13.7 (IN), U56.20 (2Q6)
/ID/Ins_ID14: U11.6 (IN), U12.6 (IN), U13.6 (IN), U15.2 (IN), U56.22 (2Q7)
/ID/Ins_ID15: U11.5 (IN), U12.5 (IN), U13.5 (IN), U15.3 (IN), U56.23 (2Q8)
/MEM/Buffer StoreOp As Bus I/O/~AssertData: TP3.1, U2.25 (2~OE), U2.48 (1~OE), U59.3
/MEM/Ctl_WB17: U4.12 (Q7), U24.1 (A0)
/MEM/Ctl_WB18: U4.13 (Q6), U28.83 (~LBL), U29.83 (~LBL)
/MEM/Ctl_WB19: U4.14 (Q5), U28.84 (~UBL), U29.84 (~UBL)
/MEM/Ctl_WB20: U4.15 (Q4), U27.1
/MEM/SelC_WB0: U4.16 (Q3), U28.66 (A0L), U29.66 (A0L)
/MEM/SelC_WB1: U4.17 (Q2), U28.67 (A1L), U29.67 (A1L)
/MEM/SelC_WB2: U4.18 (Q1), U28.68 (A2L), U29.68 (A2L)
/MEM/StoreOp_WB0: U9.2 (1Q1), U26.47 (1A1)
/MEM/StoreOp_WB1: U9.3 (1Q2), U26.46 (1A2)
/MEM/StoreOp_WB2: U9.5 (1Q3), U26.44 (1A3)
/MEM/StoreOp_WB3: U9.6 (1Q4), U26.43 (1A4)
/MEM/StoreOp_WB4: U9.8 (1Q5), U26.41 (1A5)
/MEM/StoreOp_WB5: U9.9 (1Q6), U26.40 (1A6)
/MEM/StoreOp_WB6: U9.11 (1Q7), U26.38 (1A7)
/MEM/StoreOp_WB7: U9.12 (1Q8), U26.37 (1A8)
/MEM/StoreOp_WB8: U9.13 (2Q1), U26.36 (2A1)
/MEM/StoreOp_WB9: U9.14 (2Q2), U26.35 (2A2)
/MEM/StoreOp_WB10: U9.16 (2Q3), U26.33 (2A3)
/MEM/StoreOp_WB11: U9.17 (2Q4), U26.32 (2A4)
/MEM/StoreOp_WB12: U9.19 (2Q5), U26.30 (2A5)
/MEM/StoreOp_WB13: U9.20 (2Q6), U26.29 (2A6)
/MEM/StoreOp_WB14: U9.22 (2Q7), U26.27 (2A7)
/MEM/StoreOp_WB15: U9.23 (2Q8), U26.26 (2A8)
/MEM/Y_WB0: U10.2 (1Q1), U25.47 (1A1)
/MEM/Y_WB1: U10.3 (1Q2), U25.46 (1A2)
/MEM/Y_WB2: U10.5 (1Q3), U25.44 (1A3)
/MEM/Y_WB3: U10.6 (1Q4), U25.43 (1A4)
/MEM/Y_WB4: U10.8 (1Q5), U25.41 (1A5)
/MEM/Y_WB5: U10.9 (1Q6), U25.40 (1A6)
/MEM/Y_WB6: U10.11 (1Q7), U25.38 (1A7)
/MEM/Y_WB7: U10.12 (1Q8), U25.37 (1A8)
/MEM/Y_WB8: U10.13 (2Q1), U25.36 (2A1)
/MEM/Y_WB9: U10.14 (2Q2), U25.35 (2A2)
/MEM/Y_WB10: U10.16 (2Q3), U25.33 (2A3)
/MEM/Y_WB11: U10.17 (2Q4), U25.32 (2A4)
/MEM/Y_WB12: U10.19 (2Q5), U25.30 (2A5)
/MEM/Y_WB13: U10.20 (2Q6), U25.29 (2A6)
/MEM/Y_WB14: U10.22 (2Q7), U25.27 (2A7)
/MEM/Y_WB15: U10.23 (2Q8), U25.26 (2A8)
/MEM/~AssertCtl: U1.19 (CE), U59.2, U60.4
/Memory/Addr0: IC1.92 (A0L), J4.7, R17.1, TP69.1, U3.47 (1A1), U61.1 (IN/CLK)
/Memory/Addr1: IC1.93 (A1L), J4.8, R19.1, TP71.1, U3.46 (1A2), U61.2 (IN)
/Memory/Addr2: IC1.94 (A2L), J4.9, R21.1, TP73.1, U3.44 (1A3), U61.3 (IN)
/Memory/Addr3: IC1.95 (A3L), J4.10, R23.1, TP75.1, U3.43 (1A4), U61.4 (IN)
/Memory/Addr4: IC1.96 (A4L), J4.13, R25.1, TP77.1, U3.41 (1A5), U61.5 (IN)
/Memory/Addr5: IC1.97 (A5L), J4.14, R27.1, TP79.1, U3.40 (1A6), U61.6 (IN)
/Memory/Addr6: IC1.98 (A6L), J4.15, R30.1, TP82.1, U3.38 (1A7), U61.7 (IN)
/Memory/Addr7: IC1.99 (A7L), J4.16, R33.1, TP85.1, U3.37 (1A8), U61.8 (IN)
/Memory/Addr8: IC1.100 (A8L), J4.19, R36.1, TP88.1, U3.36 (2A1), U61.9 (IN)
/Memory/Addr9: IC1.1 (A9L), J4.20, R38.1, TP90.1, U3.35 (2A2), U61.10 (IN)
/Memory/Addr10: IC1.2 (A10L), J4.21, R41.1, TP93.1, U3.33 (2A3), U61.11 (IN)
/Memory/Addr11: IC1.3 (A11L), J4.22, R44.1, TP96.1, U3.32 (2A4), U61.13 (IN/~OE)
/Memory/Addr12: IC1.4 (A12L), J4.25, R46.1, TP98.1, U3.30 (2A5), U61.14 (I/O)
/Memory/Addr13: IC1.5 (A13L), J4.26, R48.1, TP100.1, U3.29 (2A6), U61.15 (I/O)
/Memory/Addr14: IC1.6 (A14L), J4.27, R50.1, TP102.1, U3.27 (2A7), U61.16 (I/O)
/Memory/Addr15: IC1.7 (A15L), J4.28, R52.1, TP104.1, U3.26 (2A8), U61.17 (I/O)
/Memory/Bank0: J4.1, R29.1, TP81.1, U61.18 (I/O), U62.3 (Q0)
/Memory/Bank1: J4.2, R32.1, TP84.1, U61.19 (I/O), U62.4 (Q1)
/Memory/Bank2: J4.3, R35.1, TP87.1, U61.20 (I/O), U62.5 (Q2)
/Memory/IO0: IC1.37 (I/O0L), J4.51, R18.1, TP70.1, U2.26 (2A8), U9.47 (1D1), U62.14 (D0)
/Memory/IO1: IC1.36 (I/O1L), J4.52, R20.1, TP72.1, U2.27 (2A7), U9.46 (1D2), U62.13 (D1)
/Memory/IO2: IC1.34 (I/O2L), J4.49, R22.1, TP74.1, U2.29 (2A6), U9.44 (1D3), U62.12 (D2)
/Memory/IO3: IC1.33 (I/O3L), J4.50, R24.1, TP76.1, U2.30 (2A5), U9.43 (1D4), U62.11 (D3)
/Memory/IO4: IC1.32 (I/O4L), J4.45, R26.1, TP78.1, U2.32 (2A4), U9.41 (1D5)
/Memory/IO5: IC1.31 (I/O5L), J4.46, R28.1, TP80.1, U2.33 (2A3), U9.40 (1D6)
/Memory/IO6: IC1.30 (I/O6L), J4.43, R31.1, TP83.1, U2.35 (2A2), U9.38 (1D7)
/Memory/IO7: IC1.29 (I/O7L), J4.44, R34.1, TP86.1, U2.36 (2A1), U9.37 (1D8)
/Memory/IO8: IC1.27 (I/O8L), J4.39, R37.1, TP89.1, U2.37 (1A8), U9.36 (2D1)
/Memory/IO9: IC1.26 (I/O9L), J4.40, R39.1, TP91.1, U2.38 (1A7), U9.35 (2D2)
/Memory/IO10: IC1.25 (I/O10L), J4.37, R42.1, TP94.1, U2.40 (1A6), U9.33 (2D3)
/Memory/IO11: IC1.24 (I/O11L), J4.38, R45.1, TP97.1, U2.41 (1A5), U9.32 (2D4)
/Memory/IO12: IC1.23 (I/O12L), J4.33, R47.1, TP99.1, U2.43 (1A4), U9.30 (2D5)
/Memory/IO13: IC1.22 (I/O13L), J4.34, R49.1, TP101.1, U2.44 (1A3), U9.29 (2D6)
/Memory/IO14: IC1.21 (I/O14L), J4.31, R51.1, TP103.1, U2.46 (1A2), U9.27 (2D7)
/Memory/IO15: IC1.20 (I/O15L), J4.32, R53.1, TP105.1, U2.47 (1A1), U9.26 (2D8)
/Memory/Ins_IF0: IC1.39 (I/O0R), J3.1, R1.1, U56.47 (1D1)
/Memory/Ins_IF1: IC1.40 (I/O1R), J3.2, R2.1, U56.46 (1D2)
/Memory/Ins_IF2: IC1.41 (I/O2R), J3.3, R3.1, U56.44 (1D3)
/Memory/Ins_IF3: IC1.42 (I/O3R), J3.4, R4.1, U56.43 (1D4)
/Memory/Ins_IF4: IC1.43 (I/O4R), J3.5, R5.1, U56.41 (1D5)
/Memory/Ins_IF5: IC1.44 (I/O5R), J3.6, R6.1, U56.40 (1D6)
/Memory/Ins_IF6: IC1.45 (I/O6R), J3.7, R7.1, U56.38 (1D7)
/Memory/Ins_IF7: IC1.47 (I/O7R), J3.8, R8.1, U56.37 (1D8)
/Memory/Ins_IF8: IC1.48 (I/O8R), J3.9, R9.1, U56.36 (2D1)
/Memory/Ins_IF9: IC1.49 (I/O9R), J3.10, R10.1, U56.35 (2D2)
/Memory/Ins_IF10: IC1.51 (I/O10R), J3.11, R11.1, U56.33 (2D3)
/Memory/Ins_IF11: IC1.52 (I/O11R), J3.12, R12.1, U56.32 (2D4)
/Memory/Ins_IF12: IC1.53 (I/O12R), J3.13, R13.1, U56.30 (2D5)
/Memory/Ins_IF13: IC1.54 (I/O13R), J3.14, R14.1, U56.29 (2D6)
/Memory/Ins_IF14: IC1.55 (I/O14R), J3.15, R15.1, U56.27 (2D7)
/Memory/Ins_IF15: IC1.56 (I/O15R), J3.16, R16.1, U56.26 (2D8)
/Memory/PC0: IC1.84 (A0R), J2.1, U53.1 (A0), U53.43 (F0), U55.47 (1D1)
/Memory/PC1: IC1.83 (A1R), J2.2, U53.2 (A1), U53.42 (F1), U55.46 (1D2)
/Memory/PC2: IC1.82 (A2R), J2.3, U53.3 (A2), U53.41 (F2), U55.44 (1D3)
/Memory/PC3: IC1.81 (A3R), J2.4, U53.4 (A3), U53.40 (F3), U55.43 (1D4)
/Memory/PC4: IC1.80 (A4R), J2.5, U53.5 (A4), U53.39 (F4), U55.41 (1D5)
/Memory/PC5: IC1.79 (A5R), J2.6, U53.6 (A5), U53.38 (F5), U55.40 (1D6)
/Memory/PC6: IC1.78 (A6R), J2.7, U53.7 (A6), U53.37 (F6), U55.38 (1D7)
/Memory/PC7: IC1.77 (A7R), J2.8, U53.8 (A7), U53.36 (F7), U55.37 (1D8)
/Memory/PC8: IC1.76 (A8R), J2.9, U53.9 (A8), U53.35 (F8), U55.36 (2D1)
/Memory/PC9: IC1.75 (A9R), J2.10, U53.10 (A9), U53.34 (F9), U55.35 (2D2)
/Memory/PC10: IC1.74 (A10R), J2.11, U53.11 (A10), U53.33 (F10), U55.33 (2D3)
/Memory/PC11: IC1.73 (A11R), J2.12, U53.12 (A11), U53.32 (F11), U55.32 (2D4)
/Memory/PC12: IC1.72 (A12R), J2.13, U53.13 (A12), U53.31 (F12), U55.30 (2D5)
/Memory/PC13: IC1.71 (A13R), J2.14, U53.14 (A13), U53.30 (F13), U55.29 (2D6)
/Memory/PC14: IC1.70 (A14R), J2.15, U53.15 (A14), U53.29 (F14), U55.27 (2D7)
/Memory/PC15: IC1.69 (A15R), J2.16, U53.16 (A15), U53.28 (F15), U55.26 (2D8)
/Memory/RAMEN_L: IC1.13 (CE1L), TP65.1, U60.5, U61.23 (I/O)
/Memory/RAMEN_R: IC1.63 (CE1R), J3.18, TP67.1, U60.9, U61.22 (I/O)
/Memory/ROM/FLUSH_IF: IC1.59 (~OER), J3.17, U51.3
/Memory/~RAMEN_L: IC1.12 (~CE0L), TP66.1, U60.6
/Memory/~RAMEN_R: IC1.64 (~CE0R), TP68.1, U60.8
/Operand Forwarding A/A_ID0: U45.2 (1B1), U46.2 (1B1), U47.2 (1B1), U57.47 (1D1)
/Operand Forwarding A/A_ID1: U45.3 (1B2), U46.3 (1B2), U47.3 (1B2), U57.46 (1D2)
/Operand Forwarding A/A_ID2: U45.5 (1B3), U46.5 (1B3), U47.5 (1B3), U57.44 (1D3)
/Operand Forwarding A/A_ID3: U45.6 (1B4), U46.6 (1B4), U47.6 (1B4), U57.43 (1D4)
/Operand Forwarding A/A_ID4: U45.8 (1B5), U46.8 (1B5), U47.8 (1B5), U57.41 (1D5)
/Operand Forwarding A/A_ID5: U45.9 (1B6), U46.9 (1B6), U47.9 (1B6), U57.40 (1D6)
/Operand Forwarding A/A_ID6: U45.11 (1B7), U46.11 (1B7), U47.11 (1B7), U57.38 (1D7)
/Operand Forwarding A/A_ID7: U45.12 (1B8), U46.12 (1B8), U47.12 (1B8), U57.37 (1D8)
/Operand Forwarding A/A_ID8: U45.13 (2B1), U46.13 (2B1), U47.13 (2B1), U57.36 (2D1)
/Operand Forwarding A/A_ID9: U45.14 (2B2), U46.14 (2B2), U47.14 (2B2), U57.35 (2D2)
/Operand Forwarding A/A_ID10: U45.16 (2B3), U46.16 (2B3), U47.16 (2B3), U57.33 (2D3)
/Operand Forwarding A/A_ID11: U45.17 (2B4), U46.17 (2B4), U47.17 (2B4), U57.32 (2D4)
/Operand Forwarding A/A_ID12: U45.19 (2B5), U46.19 (2B5), U47.19 (2B5), U57.30 (2D5)
/Operand Forwarding A/A_ID13: U45.20 (2B6), U46.20 (2B6), U47.20 (2B6), U57.29 (2D6)
/Operand Forwarding A/A_ID14: U45.22 (2B7), U46.22 (2B7), U47.22 (2B7), U57.27 (2D7)
/Operand Forwarding A/A_ID15: U45.23 (2B8), U46.23 (2B8), U47.23 (2B8), U57.26 (2D8)
/Operand Forwarding A/RegisterA0: U28.14 (I/O0R), U45.47 (1A1)
/Operand Forwarding A/RegisterA1: U28.15 (I/O1R), U45.46 (1A2)
/Operand Forwarding A/RegisterA2: U28.16 (I/O2R), U45.44 (1A3)
/Operand Forwarding A/RegisterA3: U28.18 (I/O3R), U45.43 (1A4)
/Operand Forwarding A/RegisterA4: U28.19 (I/O4R), U45.41 (1A5)
/Operand Forwarding A/RegisterA5: U28.20 (I/O5R), U45.40 (1A6)
/Operand Forwarding A/RegisterA6: U28.21 (I/O6R), U45.38 (1A7)
/Operand Forwarding A/RegisterA7: U28.26 (I/O7R), U45.37 (1A8)
/Operand Forwarding A/RegisterA8: U28.27 (I/O8R), U45.36 (2A1)
/Operand Forwarding A/RegisterA9: U28.28 (I/O9R), U45.35 (2A2)
/Operand Forwarding A/RegisterA10: U28.29 (I/O10R), U45.33 (2A3)
/Operand Forwarding A/RegisterA11: U28.30 (I/O11R), U45.32 (2A4)
/Operand Forwarding A/RegisterA12: U28.31 (I/O12R), U45.30 (2A5)
/Operand Forwarding A/RegisterA13: U28.32 (I/O13R), U45.29 (2A6)
/Operand Forwarding A/RegisterA14: U28.33 (I/O14R), U45.27 (2A7)
/Operand Forwarding A/RegisterA15: U28.35 (I/O15R), U45.26 (2A8)
/Operand Forwarding B/B_ID0: U48.2 (1B1), U49.2 (1B1), U50.2 (1B1), U58.47 (1D1)
/Operand Forwarding B/B_ID1: U48.3 (1B2), U49.3 (1B2), U50.3 (1B2), U58.46 (1D2)
/Operand Forwarding B/B_ID2: U48.5 (1B3), U49.5 (1B3), U50.5 (1B3), U58.44 (1D3)
/Operand Forwarding B/B_ID3: U48.6 (1B4), U49.6 (1B4), U50.6 (1B4), U58.43 (1D4)
/Operand Forwarding B/B_ID4: U48.8 (1B5), U49.8 (1B5), U50.8 (1B5), U58.41 (1D5)
/Operand Forwarding B/B_ID5: U48.9 (1B6), U49.9 (1B6), U50.9 (1B6), U58.40 (1D6)
/Operand Forwarding B/B_ID6: U48.11 (1B7), U49.11 (1B7), U50.11 (1B7), U58.38 (1D7)
/Operand Forwarding B/B_ID7: U48.12 (1B8), U49.12 (1B8), U50.12 (1B8), U58.37 (1D8)
/Operand Forwarding B/B_ID8: U48.13 (2B1), U49.13 (2B1), U50.13 (2B1), U58.36 (2D1)
/Operand Forwarding B/B_ID9: U48.14 (2B2), U49.14 (2B2), U50.14 (2B2), U58.35 (2D2)
/Operand Forwarding B/B_ID10: U48.16 (2B3), U49.16 (2B3), U50.16 (2B3), U58.33 (2D3)
/Operand Forwarding B/B_ID11: U48.17 (2B4), U49.17 (2B4), U50.17 (2B4), U58.32 (2D4)
/Operand Forwarding B/B_ID12: U48.19 (2B5), U49.19 (2B5), U50.19 (2B5), U58.30 (2D5)
/Operand Forwarding B/B_ID13: U48.20 (2B6), U49.20 (2B6), U50.20 (2B6), U58.29 (2D6)
/Operand Forwarding B/B_ID14: U48.22 (2B7), U49.22 (2B7), U50.22 (2B7), U58.27 (2D7)
/Operand Forwarding B/B_ID15: U48.23 (2B8), U49.23 (2B8), U50.23 (2B8), U58.26 (2D8)
/Operand Forwarding B/RegisterB0: U29.14 (I/O0R), U48.47 (1A1)
/Operand Forwarding B/RegisterB1: U29.15 (I/O1R), U48.46 (1A2)
/Operand Forwarding B/RegisterB2: U29.16 (I/O2R), U48.44 (1A3)
/Operand Forwarding B/RegisterB3: U29.18 (I/O3R), U48.43 (1A4)
/Operand Forwarding B/RegisterB4: U29.19 (I/O4R), U48.41 (1A5)
/Operand Forwarding B/RegisterB5: U29.20 (I/O5R), U48.40 (1A6)
/Operand Forwarding B/RegisterB6: U29.21 (I/O6R), U48.38 (1A7)
/Operand Forwarding B/RegisterB7: U29.26 (I/O7R), U48.37 (1A8)
/Operand Forwarding B/RegisterB8: U29.27 (I/O8R), U48.36 (2A1)
/Operand Forwarding B/RegisterB9: U29.28 (I/O9R), U48.35 (2A2)
/Operand Forwarding B/RegisterB10: U29.29 (I/O10R), U48.33 (2A3)
/Operand Forwarding B/RegisterB11: U29.30 (I/O11R), U48.32 (2A4)
/Operand Forwarding B/RegisterB12: U29.31 (I/O12R), U48.30 (2A5)
/Operand Forwarding B/RegisterB13: U29.32 (I/O13R), U48.29 (2A6)
/Operand Forwarding B/RegisterB14: U29.33 (I/O14R), U48.27 (2A7)
/Operand Forwarding B/RegisterB15: U29.35 (I/O15R), U48.26 (2A8)
/Phi1_In: J4.56, U23.3 (A1), U23.4 (A2), U23.5 (A3), U23.6 (A4)
/Phi1a: TP36.1, U23.17 (B1), U30.11 (CP), U42.25 (2CLK), U42.48 (1CLK), U43.25 (2CLK), U43.48 (1CLK), U44.25 (2CLK), U44.48 (1CLK), U53.17 (CLK), U54.1
/Phi1b: TP37.1, U4.11 (Cp), U9.25 (2CLK), U9.48 (1CLK), U10.25 (2CLK), U10.48 (1CLK), U23.16 (B2), U62.7 (Cp)
/Phi1c: TP38.1, U20.25 (2CLK), U20.48 (1CLK), U21.25 (2CLK), U21.48 (1CLK), U22.11 (Cp), U23.15 (B3)
/Phi1d: TP39.1, U23.14 (B4), U57.25 (2CLK), U57.48 (1CLK), U58.25 (2CLK), U58.48 (1CLK)
/Phi2: TP35.1, U23.18 (B0), U27.2
/Phi2_In: J4.55, U23.2 (A0)
/System Bus Connector/~MemLoad: IC1.17 (~OEL), J4.62, R43.1, TP95.1, U1.17 (B1)
/System Bus Connector/~MemStore: IC1.16 (R/~WL), J4.61, R40.1, TP92.1, U1.18 (B0), U62.10 (E2)
/Write Back and Register File/Select Write Back Source/C0: TP40.1, U25.2 (1B1), U26.2 (1B1), U28.90 (I/O0L), U29.90 (I/O0L)
/Write Back and Register File/Select Write Back Source/C1: TP41.1, U25.3 (1B2), U26.3 (1B2), U28.91 (I/O1L), U29.91 (I/O1L)
/Write Back and Register File/Select Write Back Source/C2: TP42.1, U25.5 (1B3), U26.5 (1B3), U28.93 (I/O2L), U29.93 (I/O2L)
/Write Back and Register File/Select Write Back Source/C3: TP43.1, U25.6 (1B4), U26.6 (1B4), U28.94 (I/O3L), U29.94 (I/O3L)
/Write Back and Register File/Select Write Back Source/C4: TP44.1, U25.8 (1B5), U26.8 (1B5), U28.95 (I/O4L), U29.95 (I/O4L)
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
